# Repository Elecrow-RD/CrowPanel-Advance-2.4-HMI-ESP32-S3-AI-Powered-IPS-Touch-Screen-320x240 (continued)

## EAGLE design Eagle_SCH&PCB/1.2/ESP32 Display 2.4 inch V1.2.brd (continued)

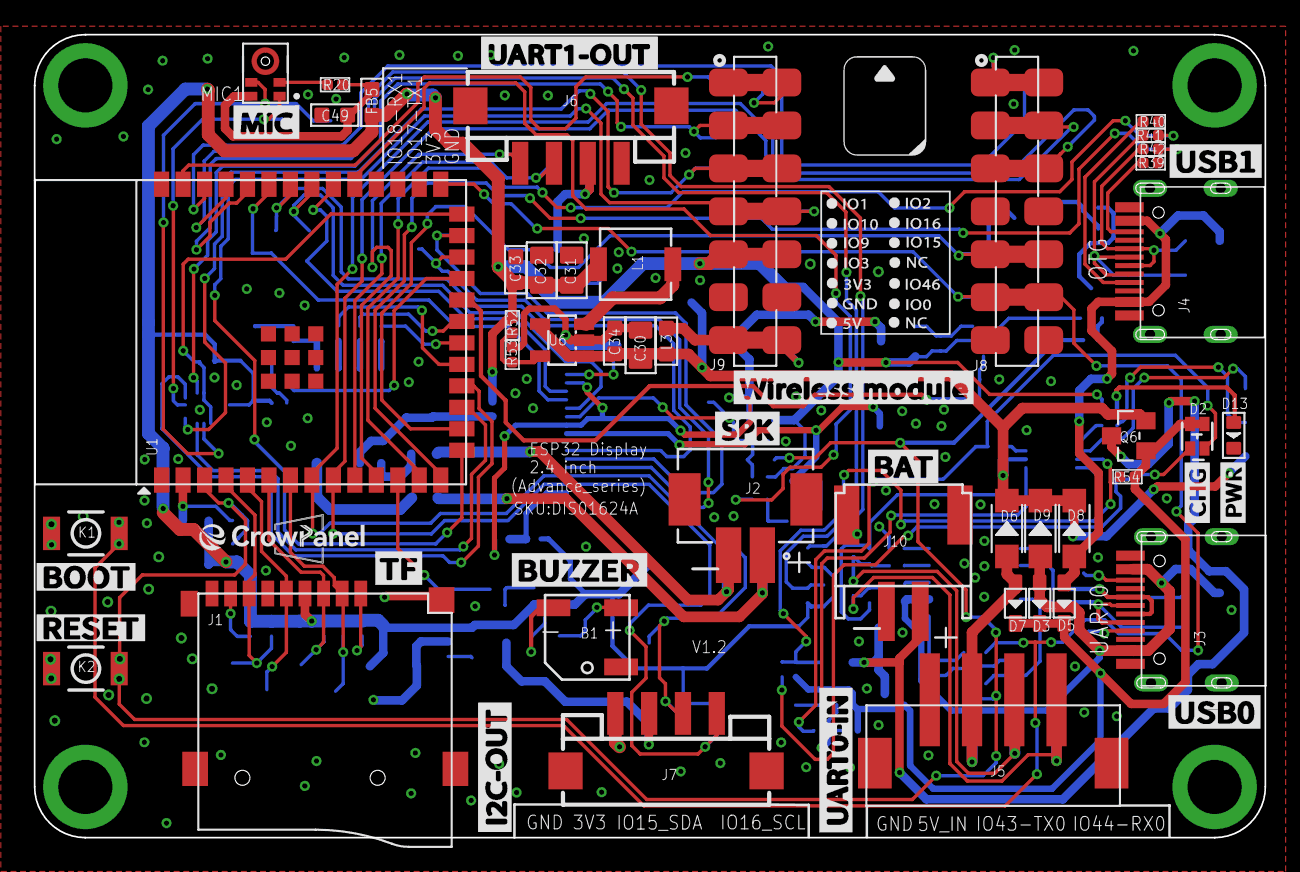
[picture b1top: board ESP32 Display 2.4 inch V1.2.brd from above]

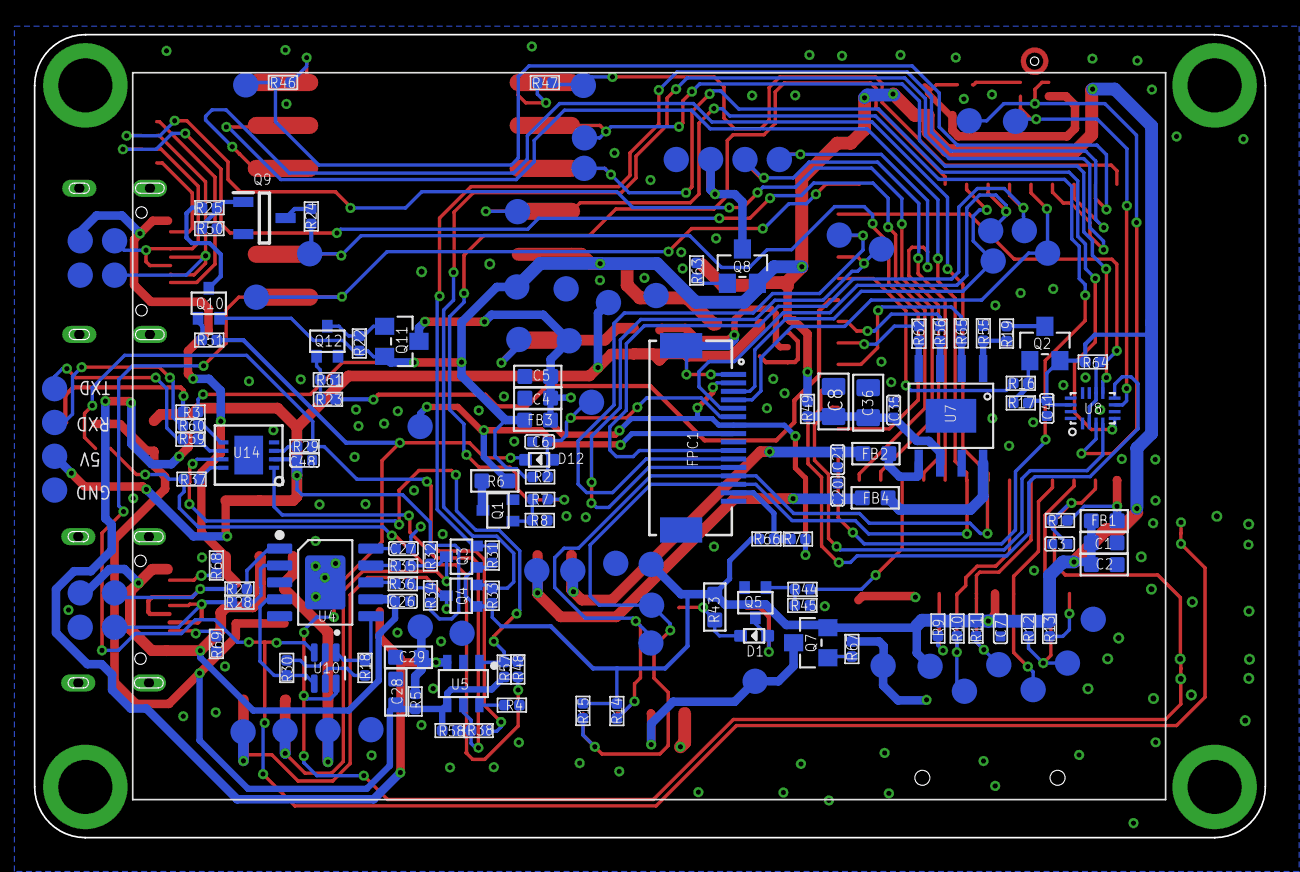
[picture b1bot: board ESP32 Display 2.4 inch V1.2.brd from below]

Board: 2 copper layers, 72.8 x 47.5 mm, 204 parts (158 on the bottom side), 117 nets.

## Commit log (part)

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2026-04-28 sync example/
2026-06-03 libraries
2026-06-08 ESP32S3
